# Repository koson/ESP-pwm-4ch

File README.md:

# ESP-pwm-4ch

ESP8266/ESP32 based board with 4x PWM output channels.

This board is designed to be driven by an Olimex ESP32-POE, ESP32-POE-ISO or Wemos D1 Mini modules running Tasmota. If you want to use the ethernet interface present on the Olimex modules you will need to compile your own Tasmota binaries enabling the corresponding features.

The design considers that the board will be mounted on a PCB DIN rail holder offered by the Brazilian manufacturer Metaltex. Check [here](https://www.metaltex.com.br/produtos/componentes/suportes/sp7-suporte-para-montagem-de-placa-de-circuito-impresso-em-trilho-din) for details.

Heatsinks are included in the design as I wasn't sure about how much power the MOSFETs would dissipate. The first tests were performed using zero ohm resistors between the drivers and the transistors. A 5A load was applied and the transistor showed no noticeable temperature elevation. In version 2 I replaced the zero ohm resistors for 22 ohm to avoid damages to the drivers, and this setup hasn't yet been tested. Given the very low switching frequency and small loads I suppose the heatsinks are still not needed.

Expect some flicker when driving LEDs with the ESP8266. It gets much more stable when using the hardware PWMs of the ESP32.

There is a preferred version of this board with 8x PWM channels and individual pins for powering groups of two outputs, what enables driving the full 5A per channel. Click [here](https://github.com/thermseekr/ESP-pwm-8ch) to check it.

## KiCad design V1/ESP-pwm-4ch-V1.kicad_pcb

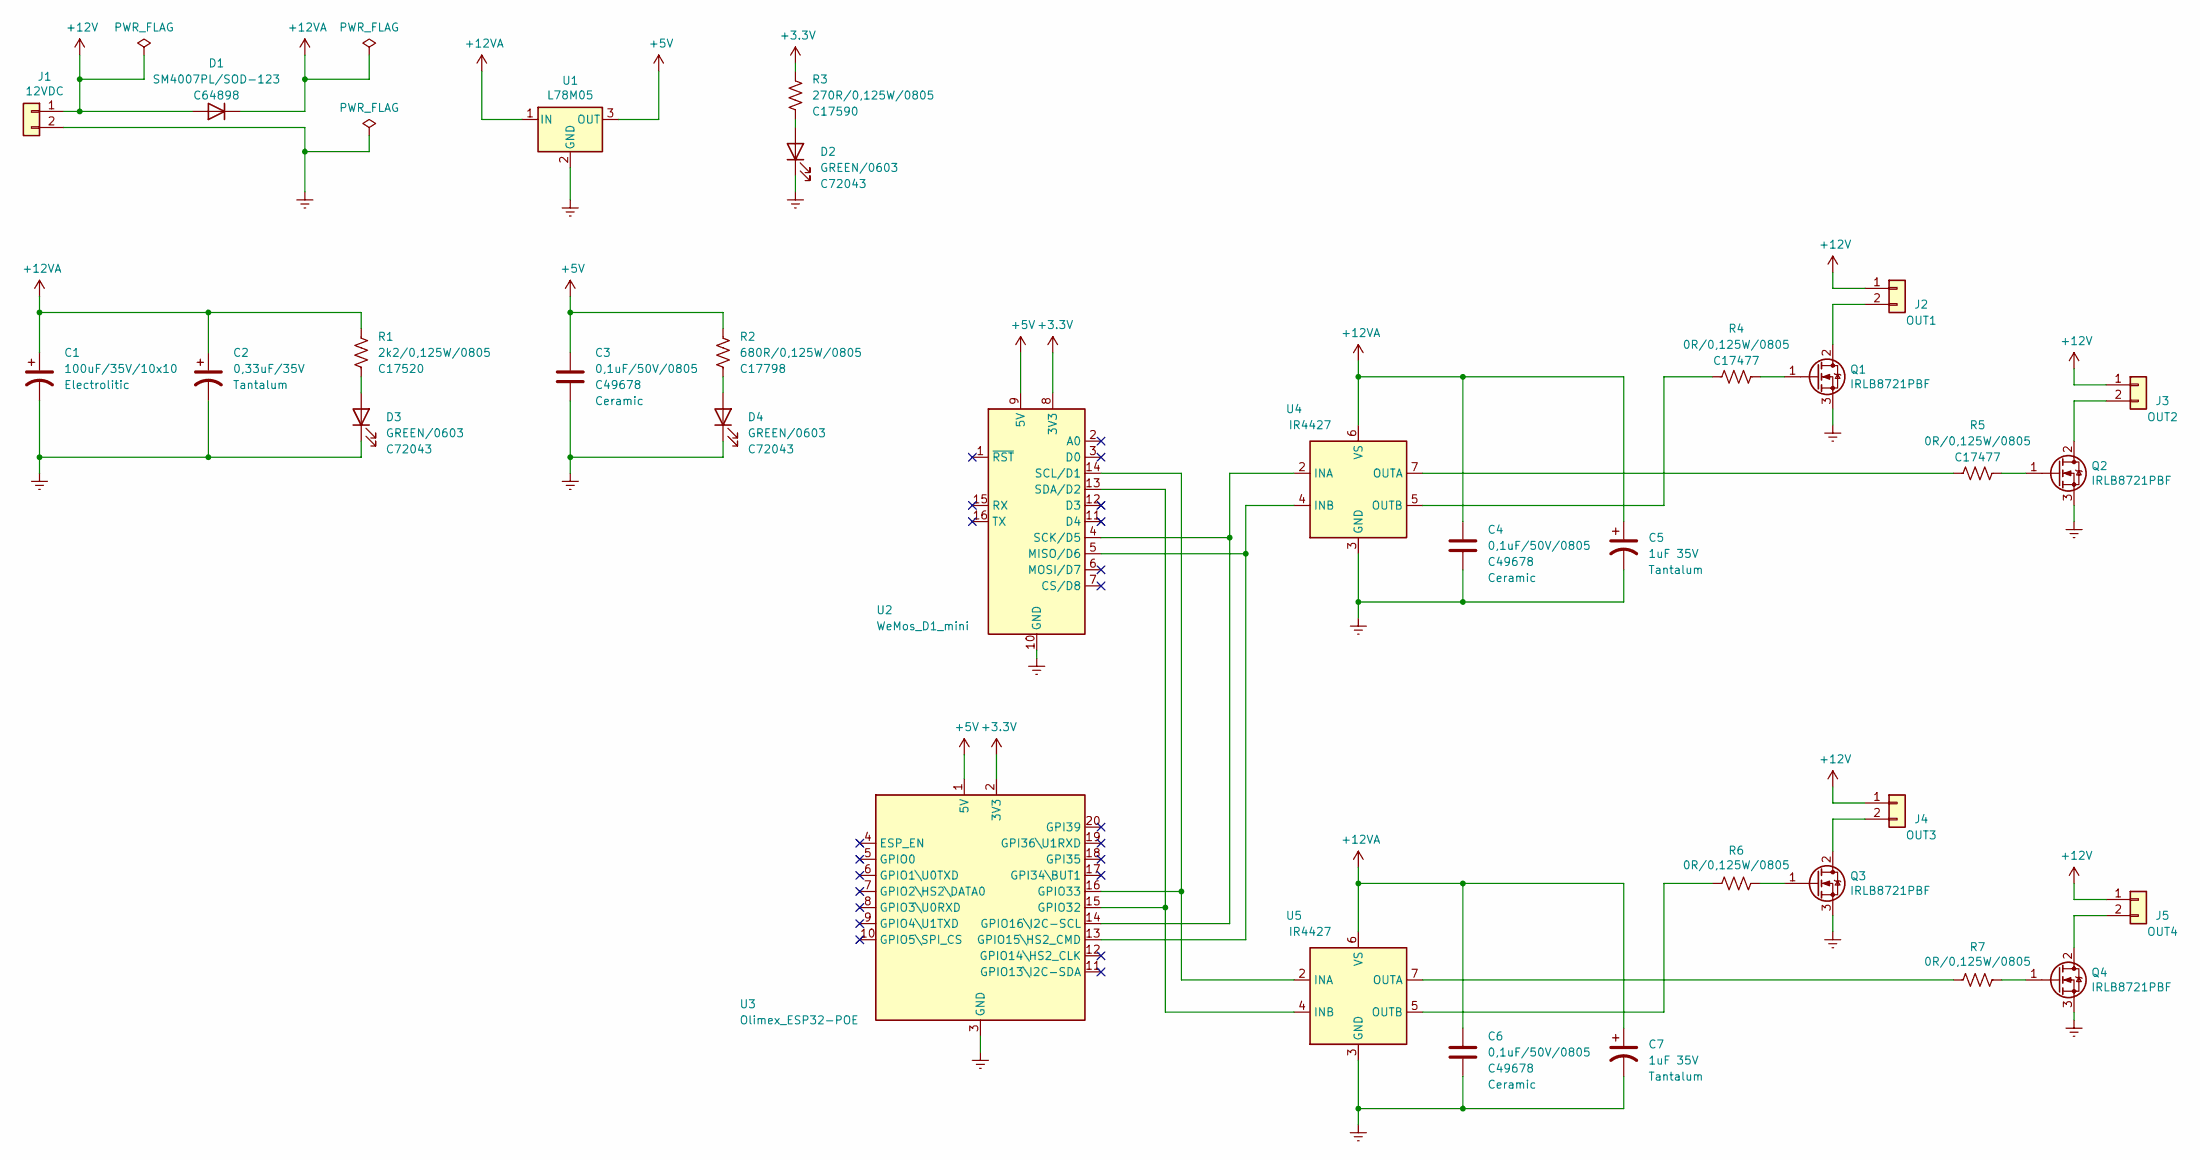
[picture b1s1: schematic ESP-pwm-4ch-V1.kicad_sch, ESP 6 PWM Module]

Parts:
C1: 100uF/35V/10x10; CP_Elec_10x10; Mfr PN MAL214097001E3; JLCPCB BOM 0
C2: 0,33uF/35V; CP_EIA-3216-18_Kemet-A_Pad1.58x1.35mm_HandSolder; Mfr PN TAJA334K035RNJ; JLCPCB BOM 0
C3, C4, C6: 0,1uF/50V/0805; C_0805_2012Metric; Mfr PN CC0805KRX7R9BB104; JLCPCB BOM 1
C5, C7: 1uF 35V; CP_EIA-3216-18_Kemet-A_Pad1.58x1.35mm_HandSolder; Mfr PN TAJA105K035TNJ; JLCPCB BOM 0
D1: SM4007PL/SOD-123; D_SOD-123; Mfr PN SM4007PL; JLCPCB BOM 1
D2, D3, D4: GREEN/0603; LED_0603_1608Metric; Mfr PN 19-217/GHC-YR1S2/3T; JLCPCB BOM 1
J1: 12VDC; TerminalBlock_Phoenix_MKDS-3-2-5.08_1x02_P5.08mm_Horizontal; Mfr PN BR902V; JLCPCB BOM 0
J2: OUT1; TerminalBlock_Phoenix_MKDS-3-2-5.08_1x02_P5.08mm_Horizontal; Mfr PN BR902V; JLCPCB BOM 0
J3: OUT2; TerminalBlock_Phoenix_MKDS-3-2-5.08_1x02_P5.08mm_Horizontal; Mfr PN BR902V; JLCPCB BOM 0
J4: OUT3; TerminalBlock_Phoenix_MKDS-3-2-5.08_1x02_P5.08mm_Horizontal; Mfr PN BR902V; JLCPCB BOM 0
J5: OUT4; TerminalBlock_Phoenix_MKDS-3-2-5.08_1x02_P5.08mm_Horizontal; Mfr PN BR902V; JLCPCB BOM 0
Q1, Q2, Q3, Q4: IRLB8721PBF; TO-220-3_Vertical; Mfr PN IRLB8721PBF; JLCPCB BOM 0
R1: 2k2/0,125W/0805; R_0805_2012Metric; Mfr PN 0805W8F2201T5E; JLCPCB BOM 1
R2: 680R/0,125W/0805; R_0805_2012Metric; Mfr PN 0805W8F6800T5E; JLCPCB BOM 1
R3: 270R/0,125W/0805; R_0805_2012Metric; Mfr PN 0805W8F2700T5E; JLCPCB BOM 1
R4, R5, R6, R7: 0R/0,125W/0805; R_0805_2012Metric; Mfr PN 0805W8F0000T5E; JLCPCB BOM 1
U1: L78M05; TO-252-2; Mfr PN L78M05ABDT-TR; JLCPCB BOM 1
U2: WeMos_D1_mini; WEMOS_D1_mini_light_pads; Mfr PN D1 Mini Node MCU; JLCPCB BOM 0
U3: Olimex_ESP32-POE; Olimex_ESP32-POE_Pads; Mfr PN ESP32-POE; JLCPCB BOM 0
U4, U5: IR4427; SOIC-8_3.9x4.9mm_P1.27mm; Mfr PN IR4427STRPBF; JLCPCB BOM 0

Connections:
+3V3: R3.1, U2.8 (3V3), U3.2 (3V3)
+5V: C3.1, R2.1, U1.3 (OUT), U2.9 (5V), U3.1 (5V)
+12V: D1.2 (A), J1.1, J2.1, J3.1, J4.1, J5.1
+12VA: C1.1, C2.1, C4.1, C5.1, C6.1, C7.1, D1.1 (K), R1.1, U1.1 (IN), U4.6 (VS), U5.6 (VS)
GNDREF: C1.2, C2.2, C3.2, C4.2, C5.2, C6.2, C7.2, D2.1 (K), D3.1 (K), D4.1 (K), J1.2, Q1.3 (S), Q2.3 (S), Q3.3 (S), Q4.3 (S), U1.2 (GND), U2.10 (GND), U3.3 (GND), U4.3 (GND), U5.3 (GND)
unnamed: D2.2 (A), R3.2
unnamed: D3.2 (A), R1.2
unnamed: D4.2 (A), R2.2
unnamed: J2.2, Q1.2 (D)
unnamed: J3.2, Q2.2 (D)
unnamed: J4.2, Q3.2 (D)
unnamed: J5.2, Q4.2 (D)
unnamed: Q1.1 (G), R4.1
unnamed: Q2.1 (G), R5.1
unnamed: Q3.1 (G), R6.1
unnamed: Q4.1 (G), R7.1
unnamed: R4.2, U4.5 (OUTB)
unnamed: R5.2, U4.7 (OUTA)
unnamed: R6.2, U5.5 (OUTB)
unnamed: R7.2, U5.7 (OUTA)
unnamed: U2.4 (SCK/D5), U3.14 (GPIO16\I2C-SCL), U4.2 (INA)
unnamed: U2.5 (MISO/D6), U3.13 (GPIO15\HS2_CMD), U4.4 (INB)
unnamed: U2.13 (SDA/D2), U3.15 (GPIO32), U5.4 (INB)
unnamed: U2.14 (SCL/D1), U3.16 (GPIO33), U5.2 (INA)

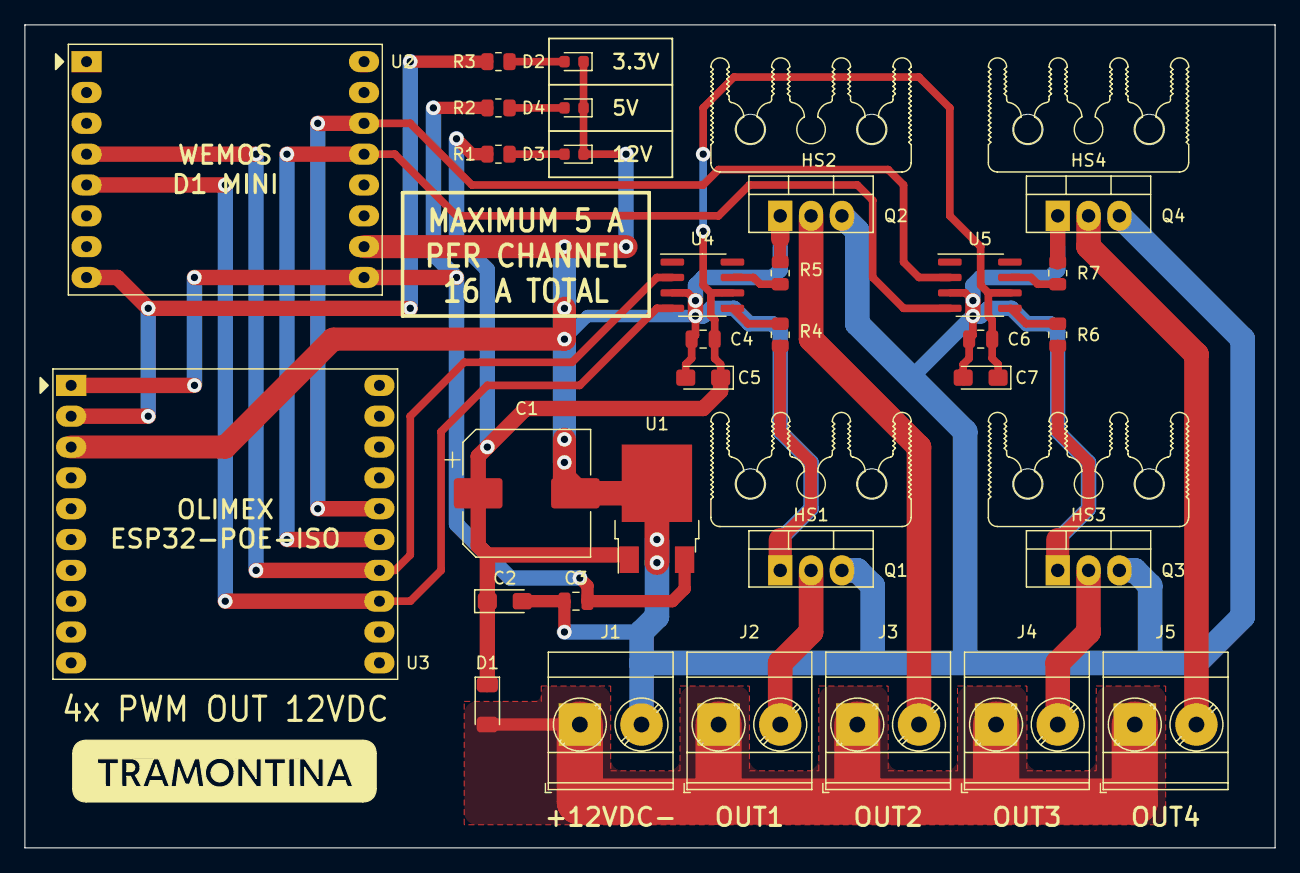
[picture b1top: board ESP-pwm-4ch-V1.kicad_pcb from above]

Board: 2 copper layers, 103.0 x 67.8 mm, 36 parts (0 on the bottom side), 24 nets.

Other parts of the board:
HS1, HS2, HS3, HS4: Heatsink_16x10x25mm_2xFixationM3

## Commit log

2022-02-02 Initial upload
2022-02-05 V2 upload
2022-02-17 kicad version update
2022-02-28 Cleanup after migration to Kicad 6
2022-03-06 kicad update
2022-03-07 V2 development
2022-03-08 tweaks
2022-03-29 work in progress
2022-04-01 Gate resistor from 0R to 22R
2022-04-01 General improvement to the routing
2022-04-01 Upload board images
2022-04-01 Ignored files
2022-04-01 Update images
2022-04-01 Reset pulled up to +3.3V
2022-04-01 Tweaking footprints
2022-04-01 PCB tweaks
2022-04-03 rename files to new schema
